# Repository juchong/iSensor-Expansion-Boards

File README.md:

# iSensor IMU Expansion Boards
## Introduction

This repository contains several expansion boards, FX3 pods, and miscellaneous circuit boards I've designed over the years to interface with ADI iSensor IMUs. All of these designs were validated at some point, but regardless, may have small issues (usually mechanical alignment)! 

### [48x, 49x Breakout Board](https://github.com/juchong/iSensor-Expansion-Boards/tree/main/48x_49x%20Breakout%20Board)

This board was designed as a smaller, more space-efficient replacement for the ADIS16IMU1/PCBZ board and provides similar functionality. All of the necessary signals are routed from the 24-pin, 1mm connector to the 16-pin, 2mm connector. 

A copy of the Rev C version of this PCB can be ordered from OshPark using this [link](https://oshpark.com/shared_projects/d1aorWWM).

### [ADXL_ADXRS Breakout Pod](https://github.com/juchong/iSensor-Expansion-Boards/tree/main/ADXL_ADXRS%20Breakout%20Pod)

This board was designed to interface with the EVAL-ADIS-FX3 (hence the "pod" nickname) and provides a generic interface for ADI accelerometers (ADXL-series devices) and gyroscopes (ADXRS-series devices) with a **digital** interface. 

A copy of the Rev A version of this PCB can be ordered from OshPark using this [link](https://oshpark.com/shared_projects/PcQ047B9).

### [FX3 Unit Test Loopback Pod](https://github.com/juchong/iSensor-Expansion-Boards/tree/main/FX3%20Unit%20Test%20Loopback%20Pod)

This board provides a compact and convenient way of verifying that the EVAL-ADIS-FX3 was manufactured correctly by looping back GPIO pins to each other. [This](https://github.com/juchong/EVAL-ADIS-FX3-Production-Test) repository contains additional software and documentation resources. 

A copy of the Rev B version of this PCB can be ordered from OshPark using this [link](https://oshpark.com/shared_projects/FAYf9S82).

### [SPI Extender](https://github.com/juchong/iSensor-Expansion-Boards/tree/main/SPI%20Extender)

These boards provided an example for using LVDS transmitters and receivers to push SPI through a CAT6 Ethernet cable (twisted pair). Using these boards, we were able to reliably communicate with an ADI IMU through 25 feet of cable. 

### [iSensor Arduino Shield](https://github.com/juchong/iSensor-Expansion-Boards/tree/main/iSensor%20Arduino%20Shield)

This shield was developed as a reference design for easily interfacing an Arduino-compatible device with most iSensor evaluation boards. The shield includes a switching regulator that can be used to power the IMU instead of relying on the host system's 3.3V supply.

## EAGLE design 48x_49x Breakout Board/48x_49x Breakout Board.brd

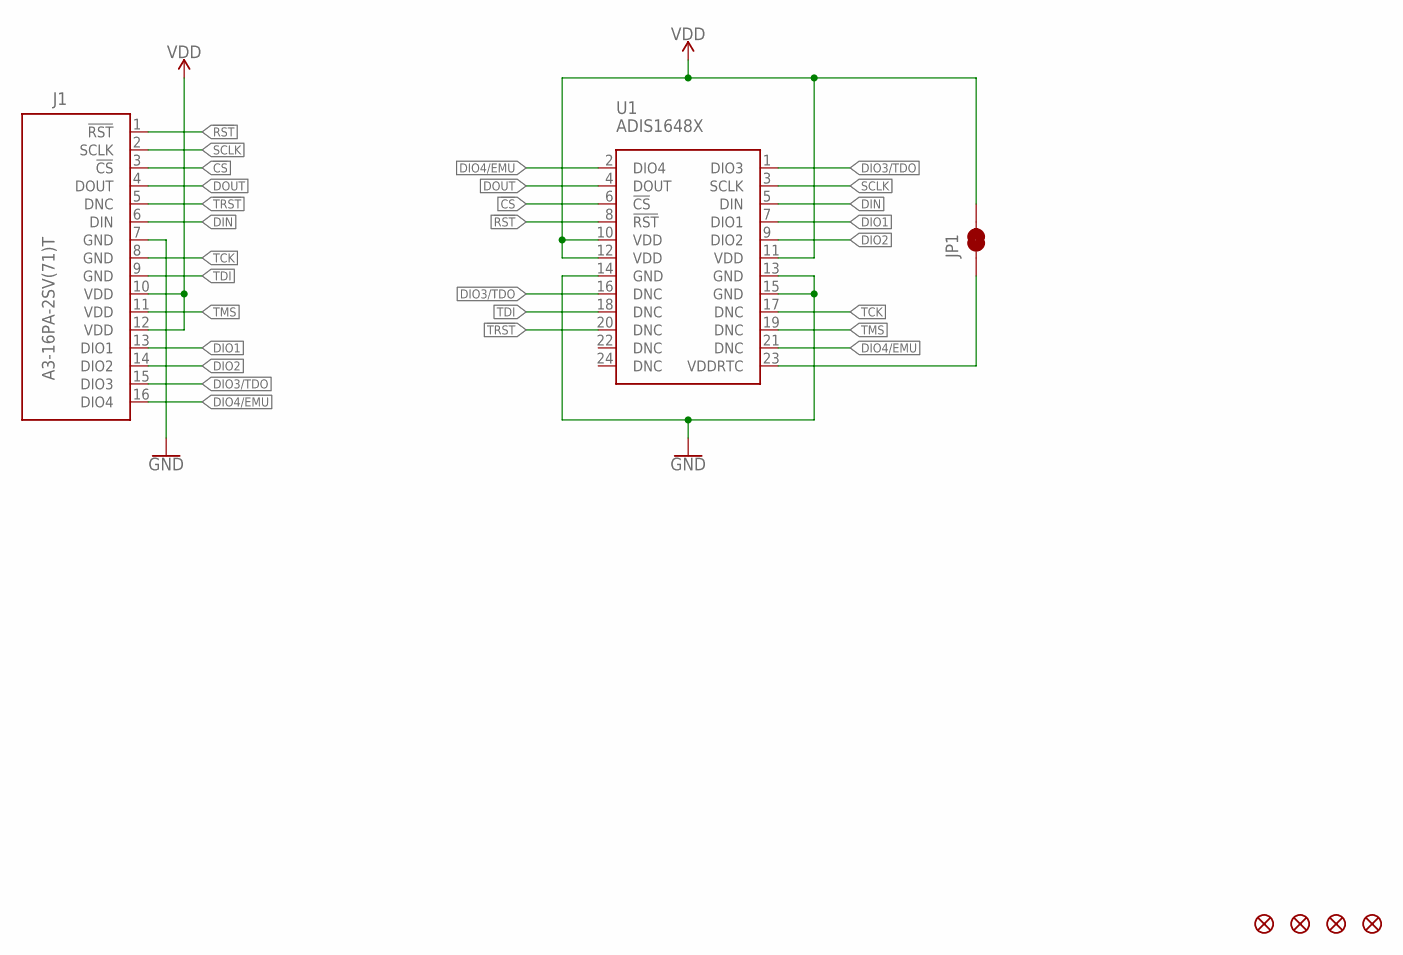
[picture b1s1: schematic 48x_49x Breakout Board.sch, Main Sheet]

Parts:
FD1, FD2, FD3, FD4: FIDUCIAL1X2; FIDUCIAL-1X2
J1: A3-16PA-2SV(71)T; A3-16PA-2SV(71)-TOP
JP1: JUMPER-SMT_2_NC_TRACE_SILK; SMT-JUMPER_2_NC_TRACE_SILK
U1: ADIS1648X

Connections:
!CS: J1.3 (!CS), U1.6 (!CS)
!RST: J1.1 (!RST), U1.8 (!RST)
!TRST: J1.5 (DNC), U1.20 (DNC)
DIN: J1.6 (DIN), U1.5 (DIN)
DIO1: J1.13 (DIO1), U1.7 (DIO1)
DIO2: J1.14 (DIO2), U1.9 (DIO2)
DIO3/TDO: J1.15 (DIO3), U1.1 (DIO3), U1.16 (DNC)
DIO4/EMU: J1.16 (DIO4), U1.2 (DIO4), U1.21 (DNC)
DOUT: J1.4 (DOUT), U1.4 (DOUT)
GND: J1.7 (GND), U1.13 (GND), U1.14 (GND), U1.15 (GND)
unnamed: JP1.1, U1.23 (VDDRTC)
SCLK: J1.2 (SCLK), U1.3 (SCLK)
TCK: J1.8 (GND), U1.17 (DNC)
TDI: J1.9 (GND), U1.18 (DNC)
TMS: J1.11 (VDD), U1.19 (DNC)
VDD: J1.10 (VDD), J1.12 (VDD), JP1.2, U1.10 (VDD), U1.11 (VDD), U1.12 (VDD)

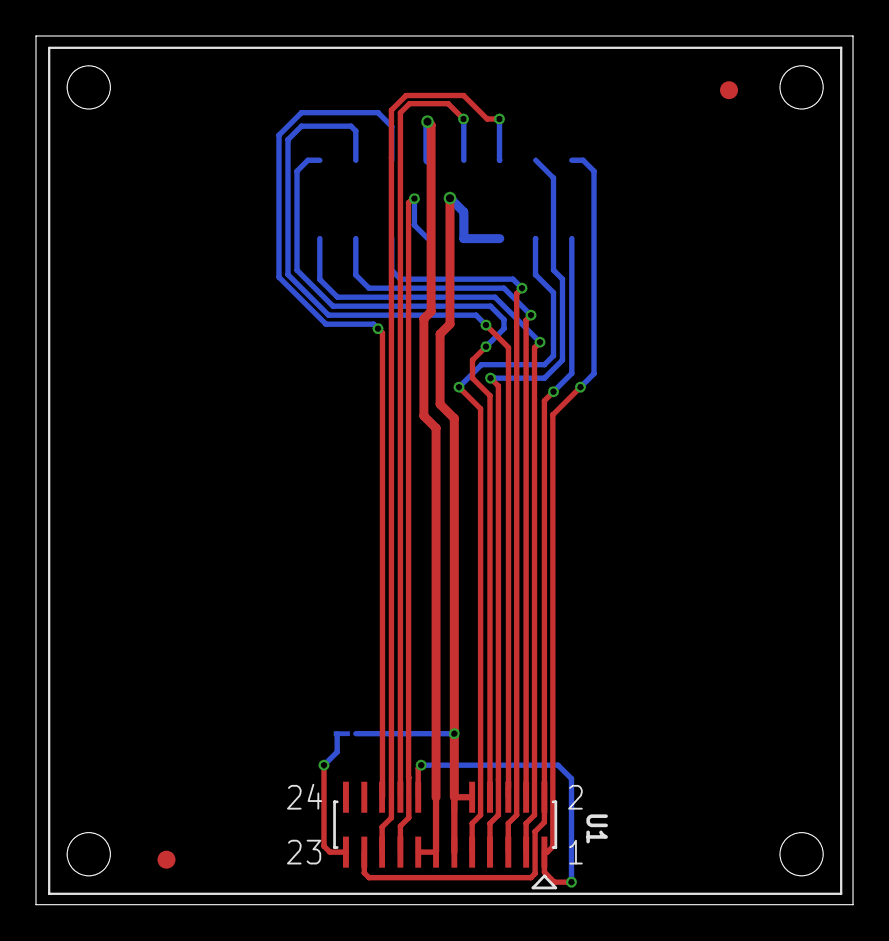
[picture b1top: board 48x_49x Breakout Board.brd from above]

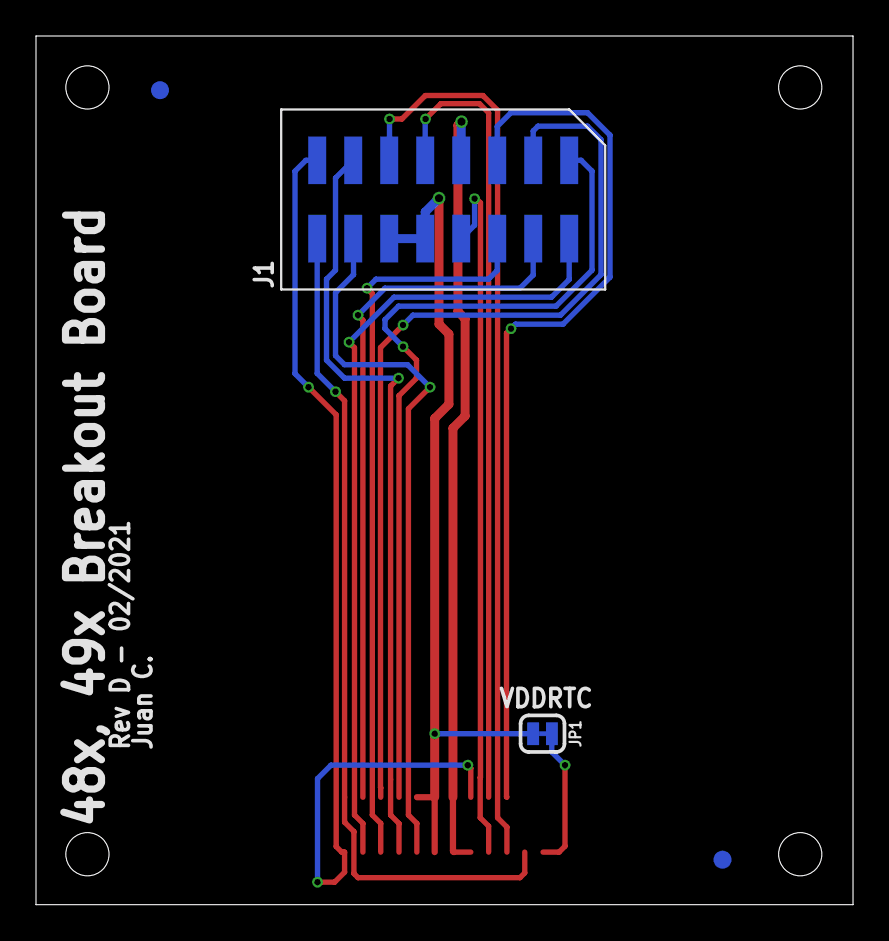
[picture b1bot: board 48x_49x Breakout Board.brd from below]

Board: 2 copper layers, 45.4 x 48.3 mm, 7 parts (4 on the bottom side), 16 nets.

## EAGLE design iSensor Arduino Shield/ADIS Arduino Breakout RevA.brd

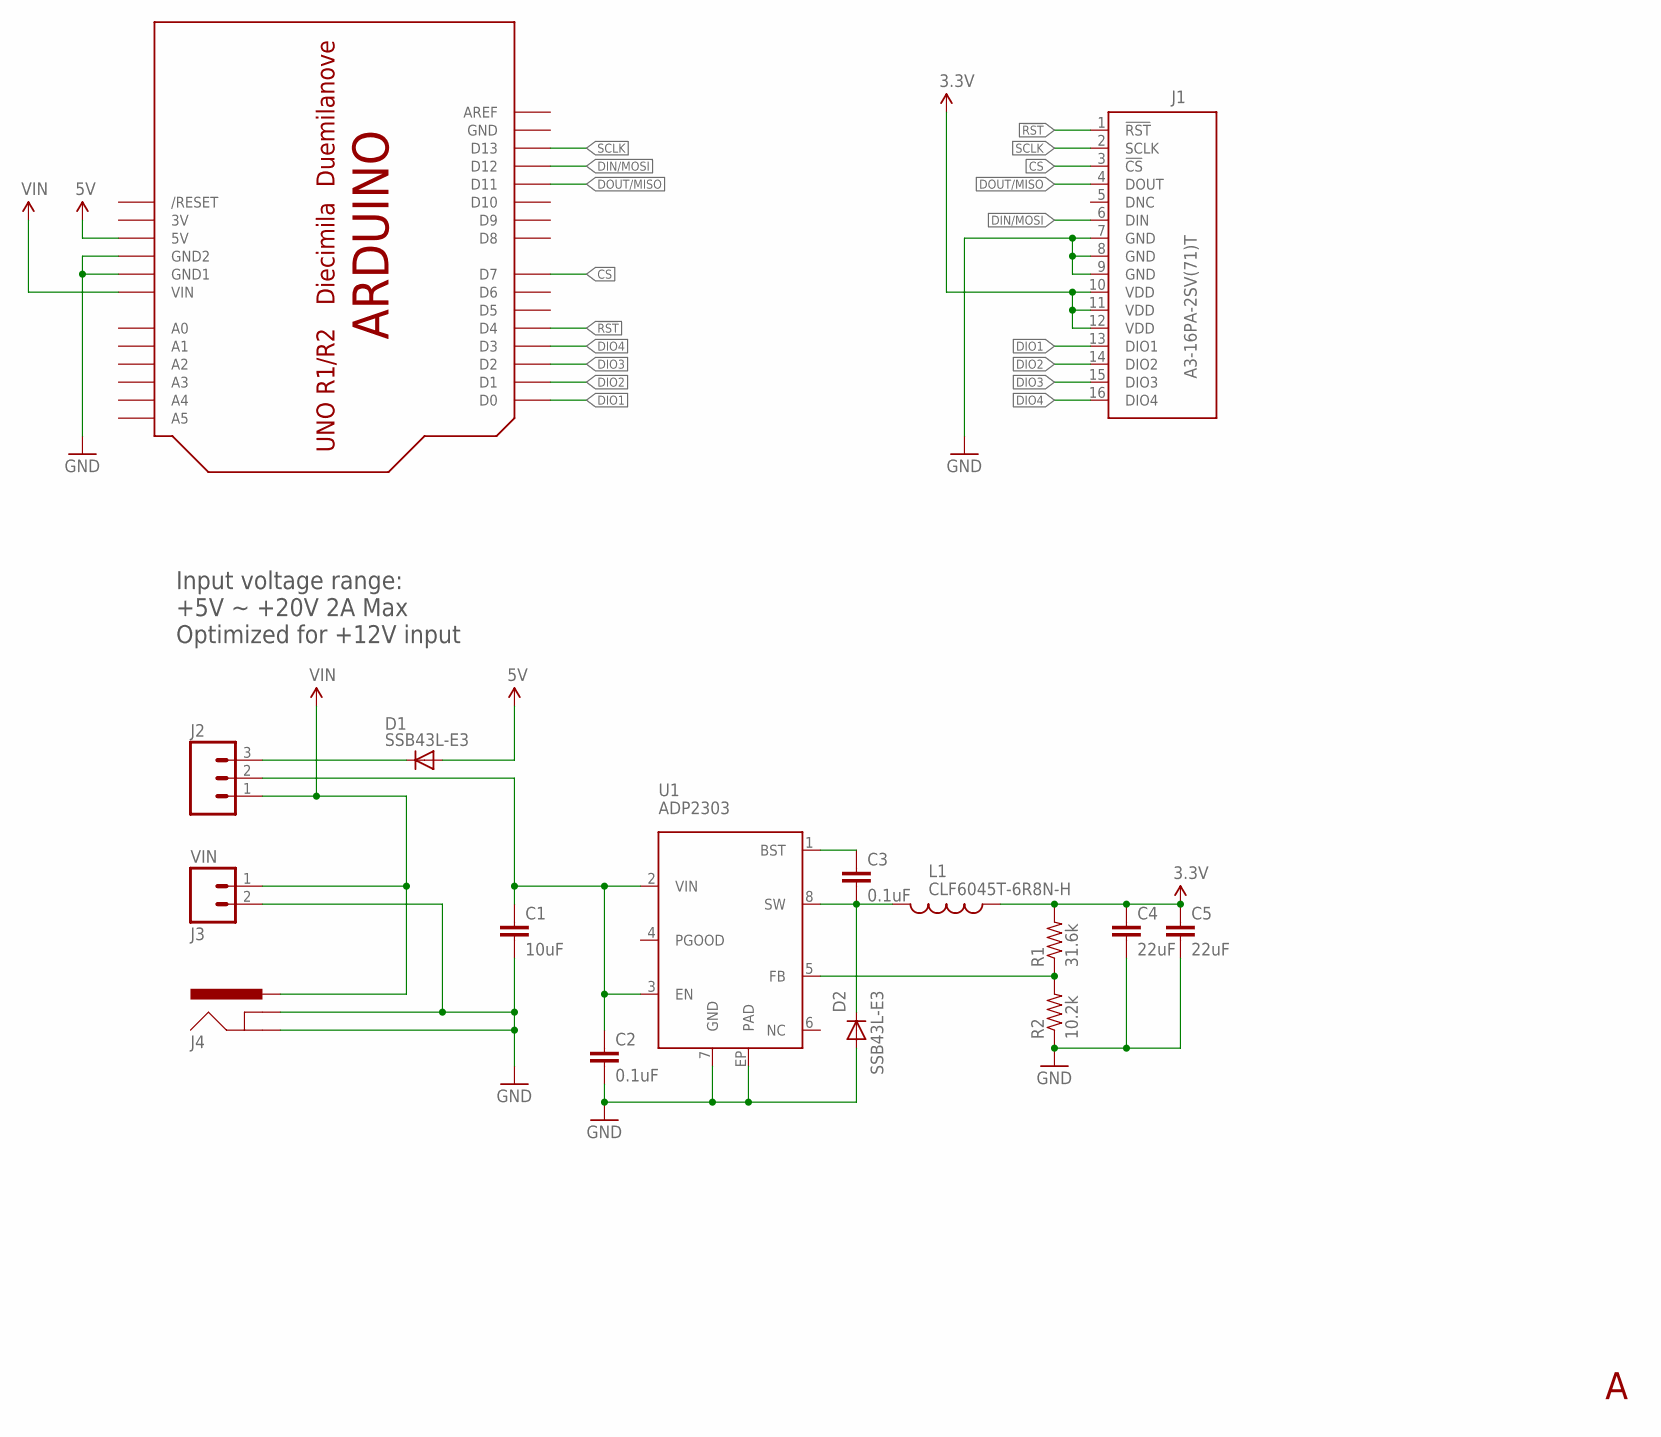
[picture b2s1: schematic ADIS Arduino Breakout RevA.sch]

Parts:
C1: 10uF; 1206; PARTNO F931C106MAA
C2, C3: 0.1uF; 0603-CAP; PARTNO CL10B104KB8NNNC
C4, C5: 22uF; 1210; PARTNO GRM32ER61C226KE20L
D1, D2: SSB43L-E3; DO214AA; PARTNO SSB43L-E3/52T
J1: A3-16PA-2SV(71)T; A3-16PA-2SV(71)-TOP; PARTNO A3-16PA-2SV(71)
J2: M03PTH; 1X03; PARTNO PREC003SAAN-RC
J3: VIN; SCREWTERMINAL-3.5MM-2; PARTNO 20020327-C021B01LF
J4: POWER_JACKPTH_LOCK; POWER_JACK_PTH_LOCK; PARTNO PJ-002AH
J5: ARDUINOUNO; ARDUINO
L1: CLF6045T-6R8N-H; CLF6045-H; PARTNO CLF6045T-6R8N-H
R1: 31.6k; 0603-RES; PARTNO ERJ-3EKF3162V
R2: 10.2k; 0603-RES; PARTNO ERJ-3EKF1022V
U1: ADP2303; SOIC-8-PAD; PARTNO ADP2303ARDZ

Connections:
3.3V: C4.1, C5.1, J1.10 (VDD), J1.11 (VDD), J1.12 (VDD), L1.P$1 (1), R1.2
3V: J5.3V
5V: D1.A, J5.5V
!RST: J1.1 (!RST), J5.D4
CS: J1.3 (!CS), J5.D7
DIN/MOSI: J1.6 (DIN), J5.D12
DIO1: J1.13 (DIO1), J5.D0
DIO2: J1.14 (DIO2), J5.D1
DIO3: J1.15 (DIO3), J5.D2
DIO4: J1.16 (DIO4), J5.D3
DOUT/MISO: J1.4 (DOUT), J5.D11
GND: C1.2, C2.2, C4.2, C5.2, D2.A, J1.7 (GND), J1.8 (GND), J1.9 (GND), J3.2, J4.GND, J4.GNDBREAK, J5.GND, J5.GND1, J5.GND2, R2.1, U1.7 (GND), U1.EP (PAD)
unnamed: R1.1, R2.2, U1.5 (FB)
unnamed: C3.2, D2.C, L1.P$2 (2), U1.8 (SW)
unnamed: C3.1, U1.1 (BST)
unnamed: C1.1, C2.1, J2.2, U1.2 (VIN), U1.3 (EN)
unnamed: D1.C, J2.3
SCLK: J1.2 (SCLK), J5.D13
VIN: J2.1, J3.1, J4.PWR, J5.VIN

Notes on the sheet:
Input voltage range: +5V ~ +20V 2A Max Optimized for +12V input

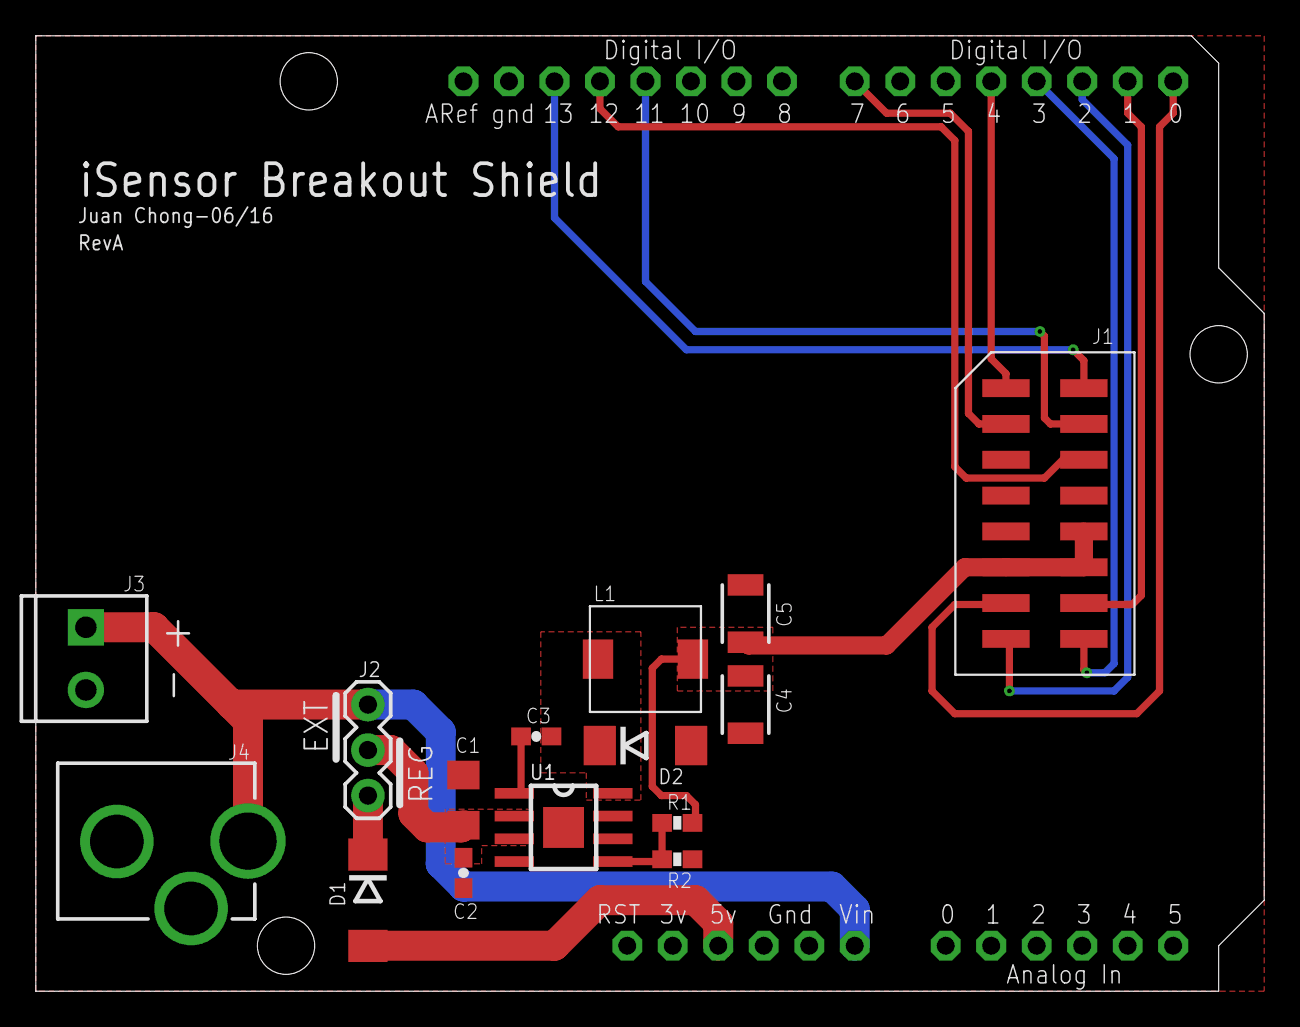
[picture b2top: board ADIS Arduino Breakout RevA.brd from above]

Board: 2 copper layers, 68.6 x 53.3 mm, 16 parts (0 on the bottom side), 18 nets.

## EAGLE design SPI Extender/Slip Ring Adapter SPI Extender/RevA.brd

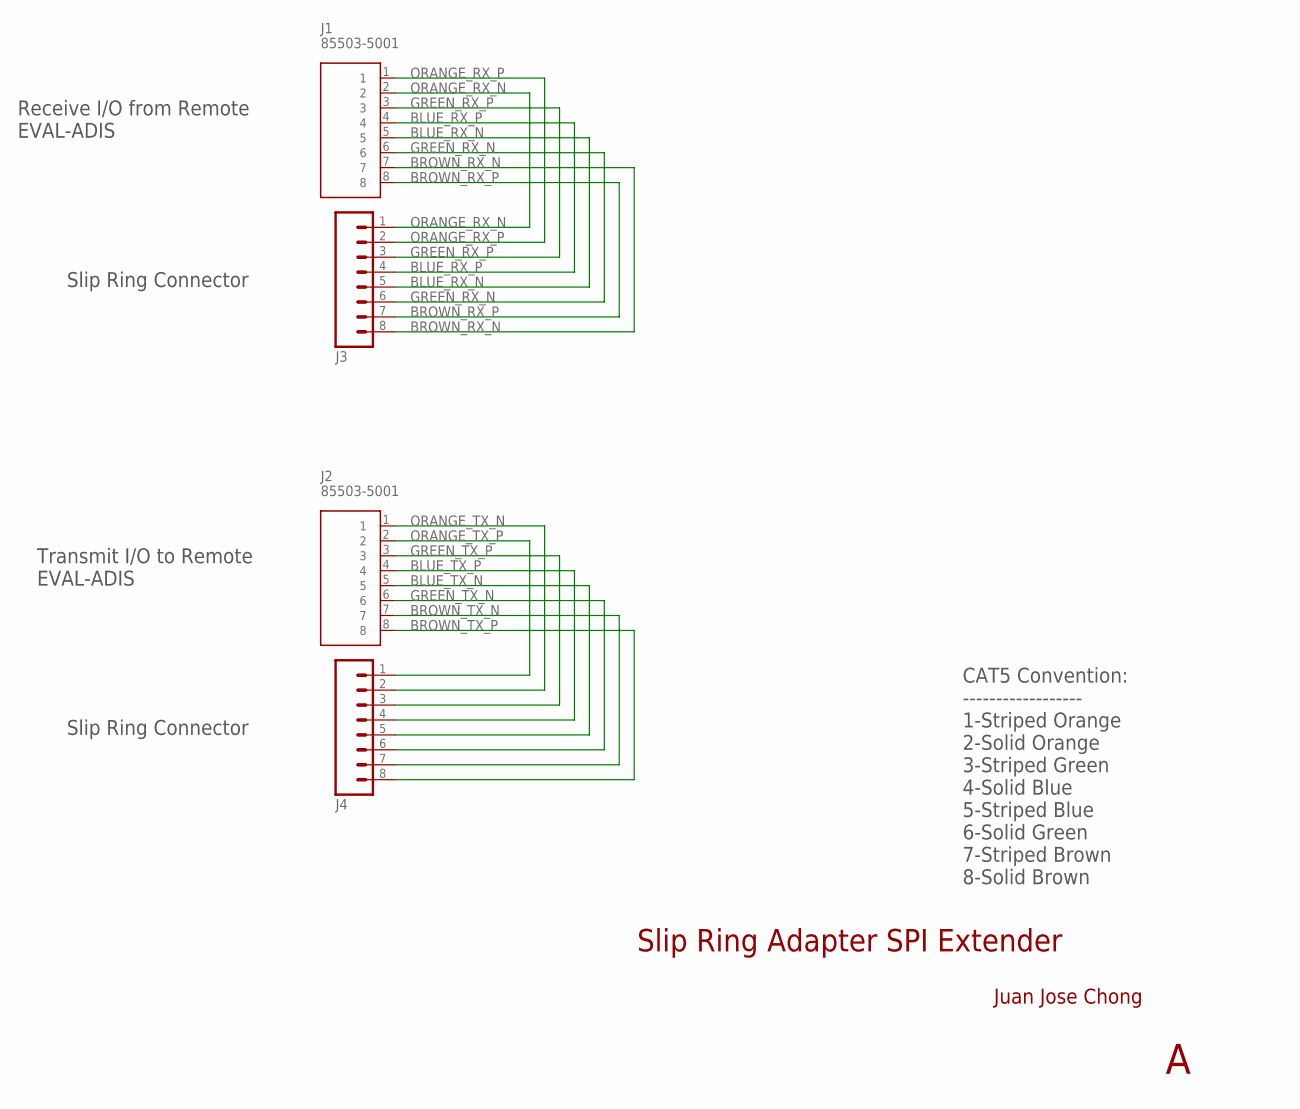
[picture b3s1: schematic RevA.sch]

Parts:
J1, J2: 85503-5001; PARTNO 855035001
J3, J4: M08LOCK; 1X08_LOCK

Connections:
BLUE_RX_N: J1.5, J3.5
BLUE_RX_P: J1.4, J3.4
BLUE_TX_N: J2.5, J4.5
BLUE_TX_P: J2.4, J4.4
BROWN_RX_N: J1.7, J3.8
BROWN_RX_P: J1.8, J3.7
BROWN_TX_N: J2.7, J4.7
BROWN_TX_P: J2.8, J4.8
GREEN_RX_N: J1.6, J3.6
GREEN_RX_P: J1.3, J3.3
GREEN_TX_N: J2.6, J4.6
GREEN_TX_P: J2.3, J4.3
ORANGE_RX_N: J1.2, J3.1
ORANGE_RX_P: J1.1, J3.2
ORANGE_TX_N: J2.1, J4.2
ORANGE_TX_P: J2.2, J4.1

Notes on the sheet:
Receive I/O from Remote EVAL-ADIS
Transmit I/O to Remote EVAL-ADIS
Slip Ring Connector
Slip Ring Adapter SPI Extender
Juan Jose Chong
CAT5 Convention: ------------------ 1-Striped Orange 2-Solid Orange 3-Striped Green 4-Solid Blue 5-Striped Blue 6-Solid Green 7-Striped Brown 8-Solid Brown

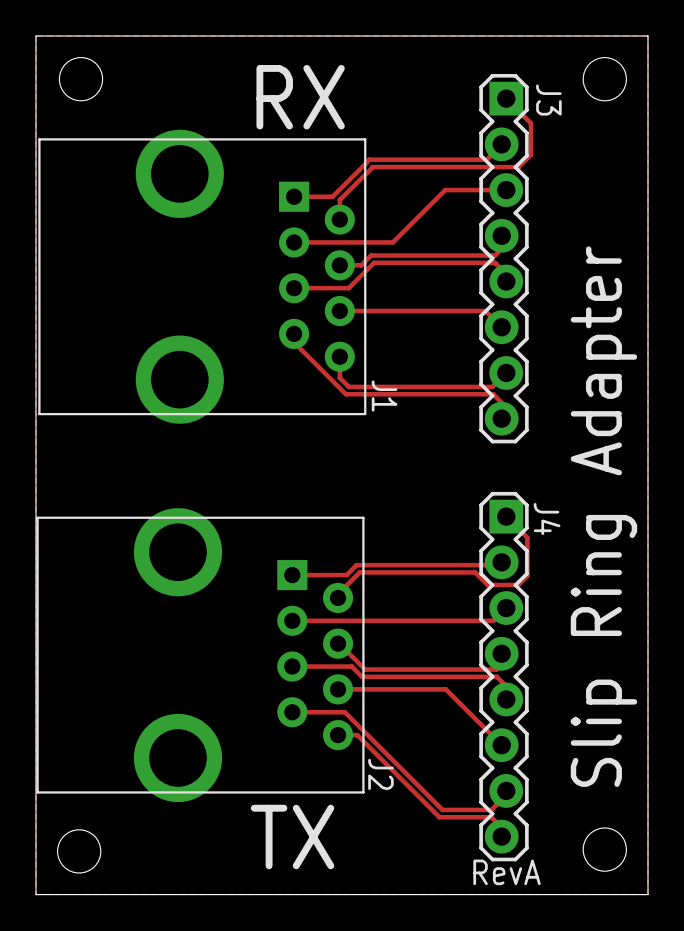
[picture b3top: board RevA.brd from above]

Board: 2 copper layers, 34.0 x 47.7 mm, 4 parts (0 on the bottom side), 16 nets.

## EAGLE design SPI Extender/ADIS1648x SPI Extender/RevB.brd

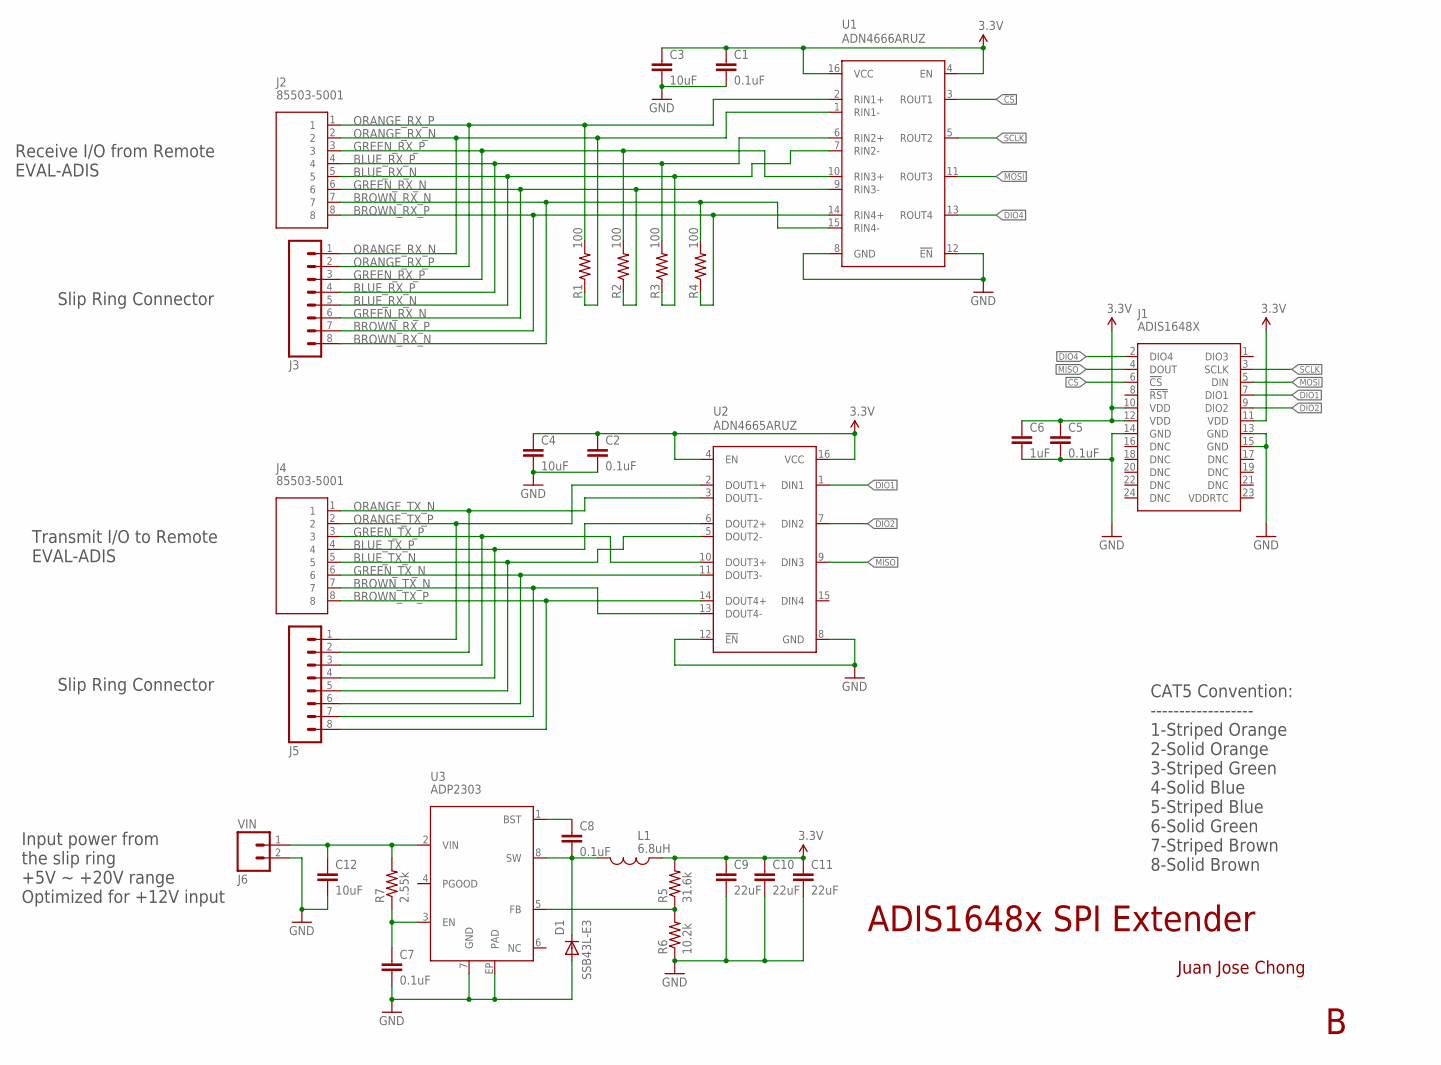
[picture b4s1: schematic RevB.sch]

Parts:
C1, C2, C5, C7, C8: 0.1uF; 0603-CAP; PARTNO CL10B104KB8NNNC
C3, C4: 10uF; 1206; PARTNO F931C106MAA
C6: 1uF; 0603-CAP; PARTNO GRM188R61C105KA93D
C9, C10, C11: 22uF; 1210; PARTNO TLJA476M010R0600
C12: 10uF; 1206; PARTNO TLJA476M010R0600
D1: SSB43L-E3; DO214AA; PARTNO SSB43L-E3/52T
J1: ADIS1648X; PARTNO CLM-112-02-L-D
J2, J4: 85503-5001; PARTNO 855035001
J3, J5: M08LOCK; 1X08_LOCK; PARTNO PREC008SAAN-RC
J6: VIN; SCREWTERMINAL-3.5MM-2; PARTNO 20020327-C021B01LF
L1: 6.8uH; VLF10040; PARTNO VLF10040T-6R8N4R5
R1, R2, R3, R4: 100; 0603-RES; PARTNO ERJ-3EKF1000V
R5: 31.6k; 0603-RES; PARTNO ERJ-3EKF3162V
R6: 10.2k; 0603-RES; PARTNO ERJ-3EKF1022V
R7: 2.55k; 0603-RES; PARTNO ERJ-3EKF2551V
U1: ADN4666ARUZ; TSSOP-16; PARTNO ADN4666ARUZ
U2: ADN4665ARUZ; TSSOP-16; PARTNO ADN4665ARUZ
U3: ADP2303; SOIC-8-PAD; PARTNO ADP2303ARDZ

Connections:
3.3V: C1.1, C2.1, C3.1, C4.1, C5.1, C6.1, C9.1, C10.1, C11.1, J1.10 (VDD), J1.11 (VDD), J1.12 (VDD), L1.P$1 (1), R5.2, U1.4 (EN), U1.16 (VCC), U2.4 (EN), U2.16 (VCC)
!CS: J1.6 (!CS), U1.3 (ROUT1)
BLUE_RX_N: J2.5, J3.5, R3.1, U1.7 (RIN2-)
BLUE_RX_P: J2.4, J3.4, R3.2, U1.6 (RIN2+)
BLUE_TX_N: J4.5, J5.5, U2.5 (DOUT2-)
BLUE_TX_P: J4.4, J5.4, U2.6 (DOUT2+)
BROWN_RX_N: J2.7, J3.8, R4.2, U1.15 (RIN4-)
BROWN_RX_P: J2.8, J3.7, R4.1, U1.14 (RIN4+)
BROWN_TX_N: J4.7, J5.7, U2.13 (DOUT4-)
BROWN_TX_P: J4.8, J5.8, U2.14 (DOUT4+)
DIO1: J1.7 (DIO1), U2.1 (DIN1)
DIO2: J1.9 (DIO2), U2.7 (DIN2)
DIO4: J1.2 (DIO4), U1.13 (ROUT4)
GND: C1.2, C2.2, C3.2, C4.2, C5.2, C6.2, C7.2, C9.2, C10.2, C11.2, C12.2, D1.A, J1.13 (GND), J1.14 (GND), J1.15 (GND), J6.2, R6.1, U1.8 (GND), U1.12 (!EN), U2.8 (GND), U2.12 (!EN), U3.7 (GND), U3.EP (PAD)
GREEN_RX_N: J2.6, J3.6, R2.1, U1.9 (RIN3-)
GREEN_RX_P: J2.3, J3.3, R2.2, U1.10 (RIN3+)
GREEN_TX_N: J4.6, J5.6, U2.11 (DOUT3-)
GREEN_TX_P: J4.3, J5.3, U2.10 (DOUT3+)
MISO: J1.4 (DOUT), U2.9 (DIN3)
MOSI: J1.5 (DIN), U1.11 (ROUT3)
unnamed: C12.1, J6.1, R7.2, U3.2 (VIN)
unnamed: R5.1, R6.2, U3.5 (FB)
unnamed: C8.2, D1.C, L1.P$2 (2), U3.8 (SW)
unnamed: C8.1, U3.1 (BST)
unnamed: C7.1, R7.1, U3.3 (EN)
ORANGE_RX_N: J2.2, J3.1, R1.1, U1.1 (RIN1-)
ORANGE_RX_P: J2.1, J3.2, R1.2, U1.2 (RIN1+)
ORANGE_TX_N: J4.1, J5.2, U2.3 (DOUT1-)
ORANGE_TX_P: J4.2, J5.1, U2.2 (DOUT1+)
SCLK: J1.3 (SCLK), U1.5 (ROUT2)

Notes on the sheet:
Receive I/O from Remote EVAL-ADIS
Transmit I/O to Remote EVAL-ADIS
Slip Ring Connector
Input power from the slip ring +5V ~ +20V range Optimized for +12V input
ADIS1648x SPI Extender
Juan Jose Chong
CAT5 Convention: ------------------ 1-Striped Orange 2-Solid Orange 3-Striped Green 4-Solid Blue 5-Striped Blue 6-Solid Green 7-Striped Brown 8-Solid Brown

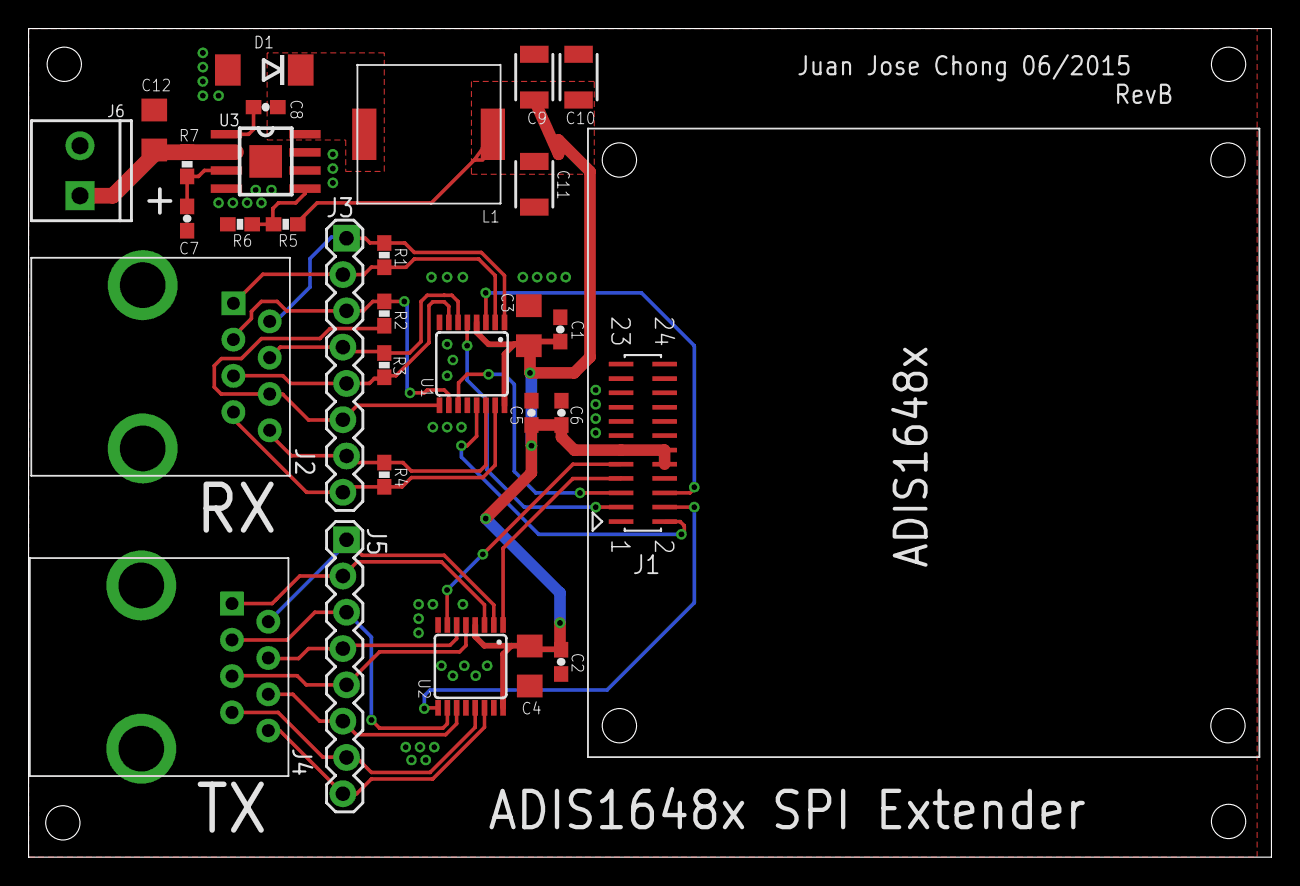
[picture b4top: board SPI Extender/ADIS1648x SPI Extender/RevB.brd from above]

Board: 2 copper layers, 87.0 x 58.0 mm, 30 parts (0 on the bottom side), 30 nets.

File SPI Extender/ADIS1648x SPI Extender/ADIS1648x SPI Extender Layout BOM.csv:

Qty-1,Part References,Value,Package,Mfg Part Num,Mfg Name,VID,Vendor Part Num,Description,Pkg Code,,XREF
2,"J3, J5",,1X08_LOCK,PREC008SAAN-RC,Sullins Connector Solutions,DK,S1012EC-08-ND,CONN HEADER .100"" SNGL STR 8POS,1X08,*,REF193
5,"C1, C2, C5, C7, C8",0.1uF,0603-CAP,CL10B104KB8NNNC,Samsung Electro-Mechanics America,DK,1276-1000-1-ND,CAP CER 0.1UF 50V 10% X7R 0603,0603-CAP,*,REF134
1,"C6",1uF,0603-CAP,GRM188R61C105KA93D,Murata Electronics North America,DK,490-1536-1-ND,CAP CER 1UF 16V 10% X5R 0603,C0603,*,REF82
1,"R7",2.55k,0603-RES,ERJ-3EKF2551V,Panasonic Electronic Components,DK,P2.55KHCT-ND,RES SMD 2.55K OHM 1% 1/10W 0603,0603-RES,*,REF190
1,"L1",6.8uH,VLF10040,VLF10040T-6R8N4R5,TDK Corporation,DK,445-3561-1-ND,FIXED IND 6.8UH 4.5A 23.8 MOHM,0.394"" L x 0.382"" W (10.00mm x 9.70mm),*,REF183
1,"R6",10.2k,0603-RES,ERJ-3EKF1022V,Panasonic Electronic Components,DK,P10.2KHCT-ND,RES SMD 10.2K OHM 1% 1/10W 0603,0603-RES,*,REF189
2,"C3, C4",10uF,1206,F931C106MAA,AVX Corporation,DK,478-8237-1-ND,CAP TANT 10UF 16V 20% 1206,1206-RES,*,REF179
1,"C12",10uF,1206,TLJA476M010R0600,AVX Corporation,DK,478-9009-1-ND,CAP TANT 47UF 10V 20% 1206,1206-RES,*,REF180
3,"C9, C10, C11",22uF,1210,TLJA476M010R0600,AVX Corporation,DK,478-9009-1-ND,CAP TANT 47UF 10V 20% 1206,1206-RES,*,REF180
1,"R5",31.6k,0603-RES,ERJ-3EKF3162V,Panasonic Electronic Components,DK,P31.6KHCT-ND,RES SMD 31.6K OHM 1% 1/10W 0603,0603-RES,*,REF188
4,"R1, R2, R3, R4",100,0603-RES,ERJ-3EKF1000V,Panasonic Electronic Components,DK,P100HCT-ND,RES SMD 100 OHM 1% 1/10W 0603,0603-RES,*,REF187
2,"J2, J4",85503-5001,85503-5001,855035001,Molex Inc.,DK,WM4016-ND,CONN MOD JACK 8P8C R/A UNSHLD,RJ45-8P8C,*,REF182
1,"J1",ADIS1648X,ADIS1648X,CLM-112-02-L-D,Samtec Inc,DK,SAM1129-12-ND,CONN RCPT LOPRO DL 24POS 1MM SMD,CLM24,*,REF192
1,"U2",ADN4665ARUZ,TSSOP-16,ADN4665ARUZ,Analog Devices Inc,DK,ADN4665ARUZ-ND,IC DRIVER DIFF LVDS QUAD 16TSSOP,TSSOP16,*,REF185
1,"U1",ADN4666ARUZ,TSSOP-16,ADN4666ARUZ,Analog Devices Inc,DK,ADN4666ARUZ-ND,IC RCVR DIFF LVDS QUAD 16TSSOP,TSSOP16,*,REF184
1,"U3",ADP2303,SOIC-8-PAD,ADP2303ARDZ,Analog Devices Inc,DK,ADP2303ARDZ-ND,IC REG BUCK ADJ 3A 8SOIC,8-SOIC-EP,*,REF186
1,"D1",SSB43L-E3,DO214AA,SSB43L-E3/52T,Vishay Semiconductor Diodes Division,DK,SSB43L-E3/52TGICT-ND,DIODE SCHOTTKY 30V 4A DO214AA,DO-214AA,*,REF181
1,"J6",VIN,SCREWTERMINAL-3.5MM-2,20020327-C021B01LF,FCI,DK,609-4725-ND,3.5MM TERMINAL BLOCK -55~110C,3.5MM,*,REF191

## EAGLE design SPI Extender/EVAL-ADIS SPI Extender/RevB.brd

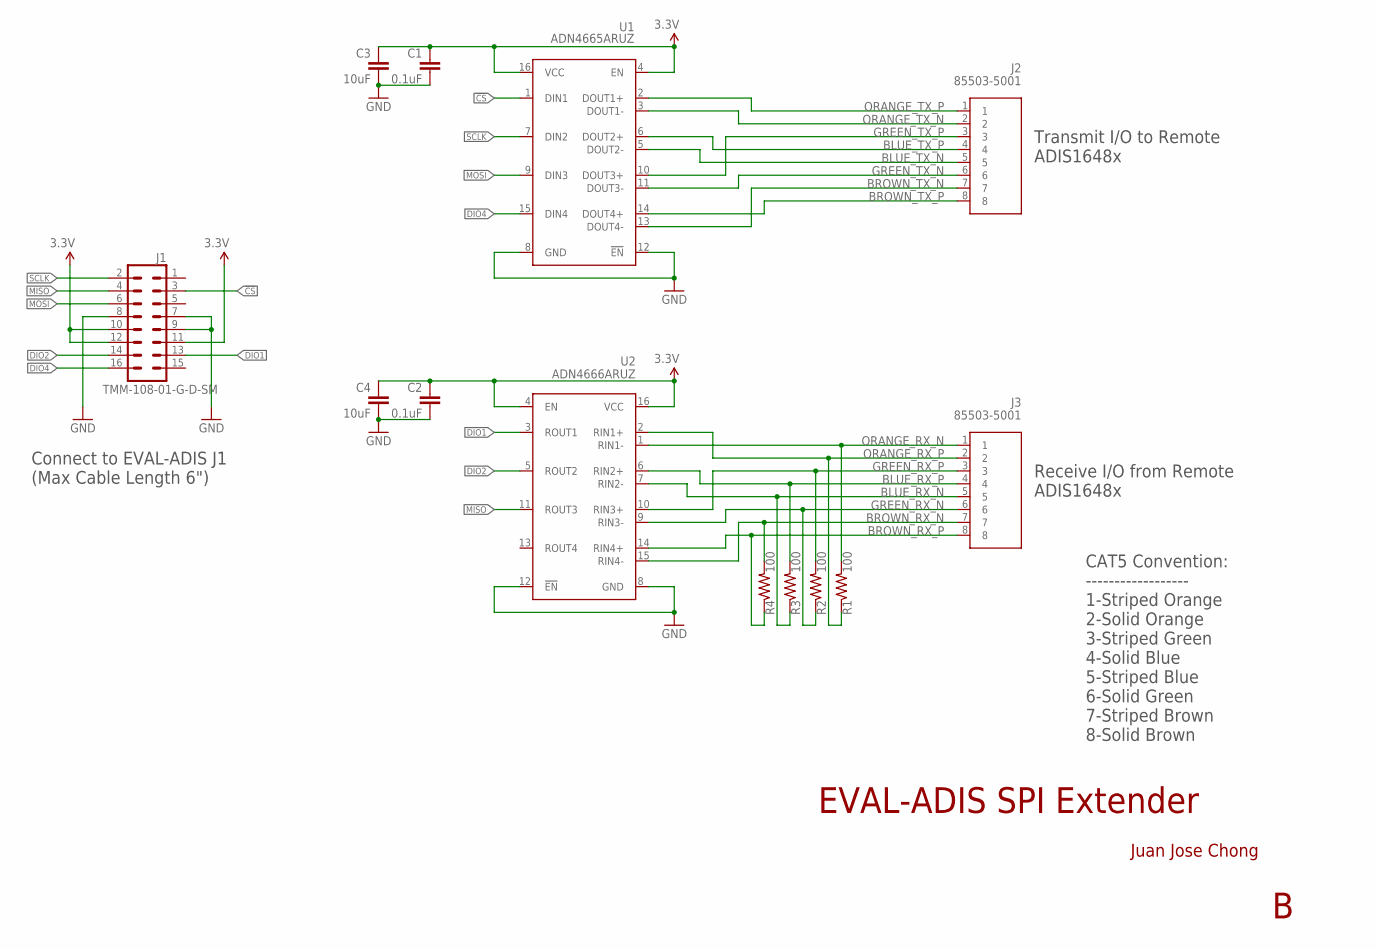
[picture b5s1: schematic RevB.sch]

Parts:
C1, C2: 0.1uF; 0805; PARTNO CL10B104KB8NNNC
C3, C4: 10uF; 1206; PARTNO F931C106MAA
J1: TMM-108-01-G-D-SM; TMM-108-XX-X-D; PARTNO TMM-108-01-G-D-SM
J2, J3: 85503-5001; PARTNO 855035001
R1, R2, R3, R4: 100; 0603-RES; PARTNO ERJ-3EKF1000V
U1: ADN4665ARUZ; TSSOP-16; PARTNO ADN4665ARUZ
U2: ADN4666ARUZ; TSSOP-16; PARTNO ADN4666ARUZ

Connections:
3.3V: C1.1, C2.1, C3.1, C4.1, J1.10, J1.11, J1.12, U1.4 (EN), U1.16 (VCC), U2.4 (EN), U2.16 (VCC)
!CS: J1.3, U1.1 (DIN1)
BLUE_RX_N: J3.5, R3.1, U2.7 (RIN2-)
BLUE_RX_P: J3.4, R3.2, U2.6 (RIN2+)
BLUE_TX_N: J2.5, U1.5 (DOUT2-)
BLUE_TX_P: J2.4, U1.6 (DOUT2+)
BROWN_RX_N: J3.7, R4.2, U2.15 (RIN4-)
BROWN_RX_P: J3.8, R4.1, U2.14 (RIN4+)
BROWN_TX_N: J2.7, U1.13 (DOUT4-)
BROWN_TX_P: J2.8, U1.14 (DOUT4+)
DIO1: J1.13, U2.3 (ROUT1)
DIO2: J1.14, U2.5 (ROUT2)
DIO4: J1.16, U1.15 (DIN4)
GND: C1.2, C2.2, C3.2, C4.2, J1.7, J1.8, J1.9, U1.8 (GND), U1.12 (!EN), U2.8 (GND), U2.12 (!EN)
GREEN_RX_N: J3.6, R2.1, U2.9 (RIN3-)
GREEN_RX_P: J3.3, R2.2, U2.10 (RIN3+)
GREEN_TX_N: J2.6, U1.11 (DOUT3-)
GREEN_TX_P: J2.3, U1.10 (DOUT3+)
MISO: J1.4, U2.11 (ROUT3)
MOSI: J1.6, U1.9 (DIN3)
ORANGE_RX_N: J3.1, R1.2, U2.1 (RIN1-)
ORANGE_RX_P: J3.2, R1.1, U2.2 (RIN1+)
ORANGE_TX_N: J2.2, U1.3 (DOUT1-)
ORANGE_TX_P: J2.1, U1.2 (DOUT1+)
SCLK: J1.2, U1.7 (DIN2)

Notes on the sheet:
EVAL-ADIS SPI Extender
Juan Jose Chong
CAT5 Convention: ------------------ 1-Striped Orange 2-Solid Orange 3-Striped Green 4-Solid Blue 5-Striped Blue 6-Solid Green 7-Striped Brown 8-Solid Brown
Connect to EVAL-ADIS J1 (Max Cable Length 6")
Transmit I/O to Remote ADIS1648x
Receive I/O from Remote ADIS1648x

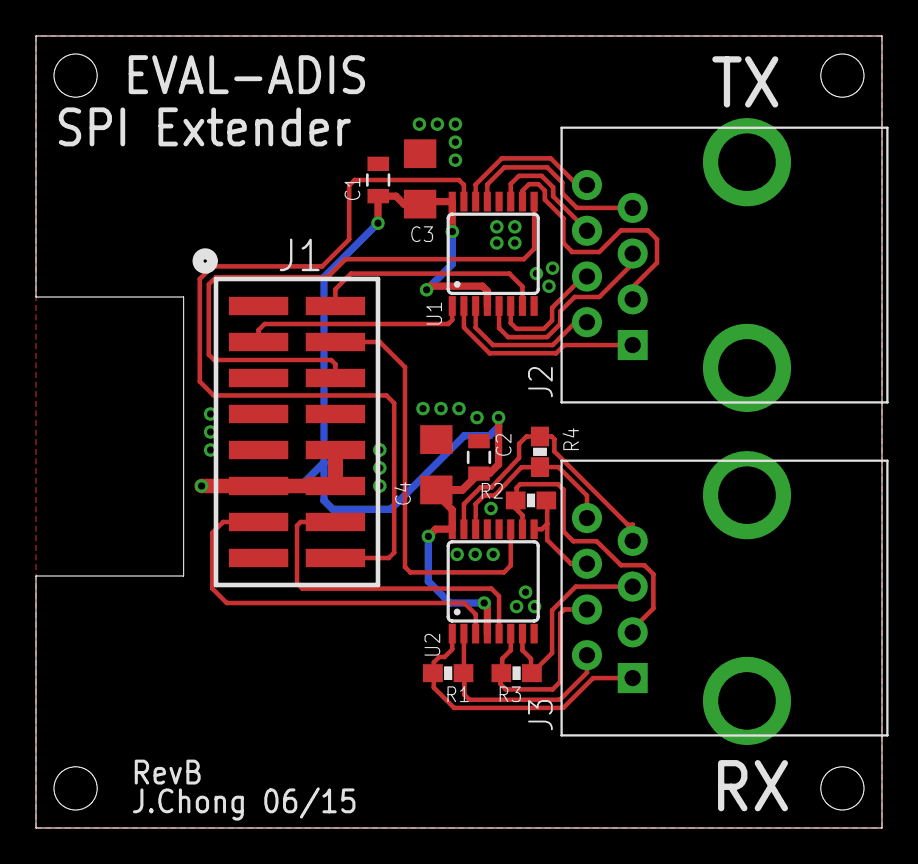
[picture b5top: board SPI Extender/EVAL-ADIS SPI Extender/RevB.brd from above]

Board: 2 copper layers, 47.0 x 44.0 mm, 13 parts (0 on the bottom side), 25 nets.

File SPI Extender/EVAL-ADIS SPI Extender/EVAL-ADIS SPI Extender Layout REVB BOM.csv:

Qty-1,Part References,Value,Package,Mfg Part Num,Mfg Name,VID,Vendor Part Num,Description,Pkg Code,,XREF
2,"C1, C2",0.1uF,0805,CL10B104KB8NNNC,Samsung Electro-Mechanics America,DK,1276-1000-1-ND,CAP CER 0.1UF 50V 10% X7R 0603,0603-CAP,*,REF134
2,"C3, C4",10uF,1206,F931C106MAA,AVX Corporation,DK,478-8237-1-ND,CAP TANT 10UF 16V 20% 1206,1206-RES,*,REF179
4,"R1, R2, R3, R4",100,0603-RES,ERJ-3EKF1000V,Panasonic Electronic Components,DK,P100HCT-ND,RES SMD 100 OHM 1% 1/10W 0603,0603-RES,*,REF187
2,"J2, J3",85503-5001,85503-5001,855035001,Molex Inc.,DK,WM4016-ND,CONN MOD JACK 8P8C R/A UNSHLD,RJ45-8P8C,*,REF182
1,"U1",ADN4665ARUZ,TSSOP-16,ADN4665ARUZ,Analog Devices Inc,DK,ADN4665ARUZ-ND,IC DRIVER DIFF LVDS QUAD 16TSSOP,TSSOP16,*,REF185
1,"U2",ADN4666ARUZ,TSSOP-16,ADN4666ARUZ,Analog Devices Inc,DK,ADN4666ARUZ-ND,IC RCVR DIFF LVDS QUAD 16TSSOP,TSSOP16,*,REF184
1,"J1",TMM-108-01-G-D-SM,TMM-108-XX-X-D,TMM-108-01-G-D-SM,Samtec Inc,DK,SAM1167-08-ND,CONN HEADER 16POS DUAL 2MM SMD,2X08 2MM SMD,*,REF194

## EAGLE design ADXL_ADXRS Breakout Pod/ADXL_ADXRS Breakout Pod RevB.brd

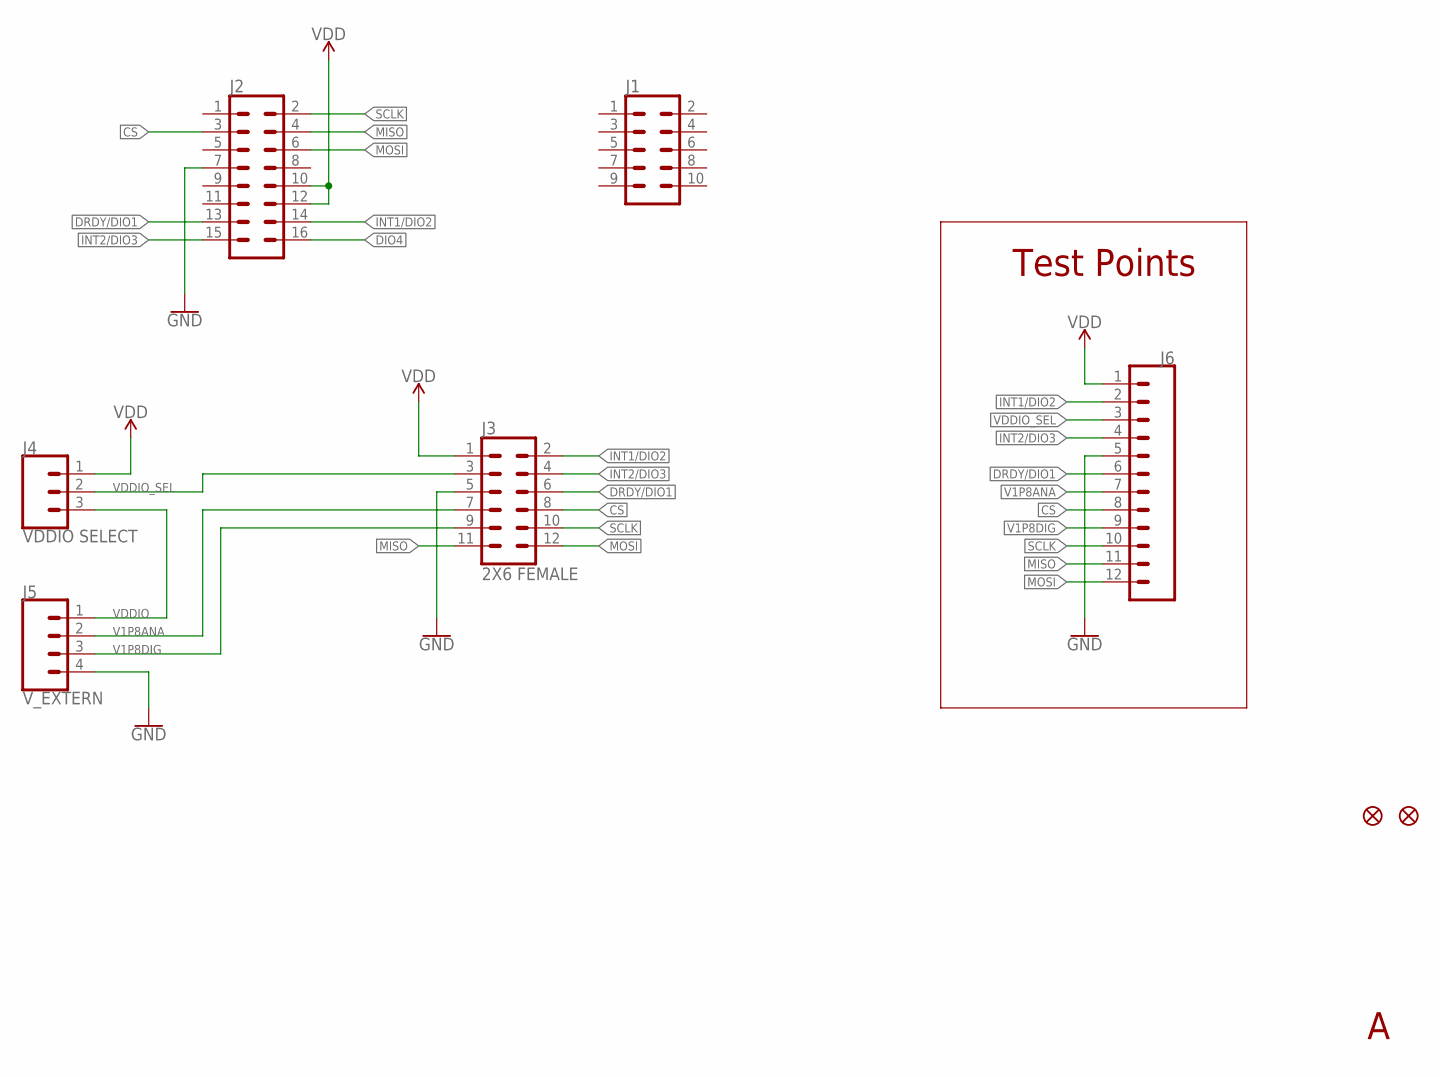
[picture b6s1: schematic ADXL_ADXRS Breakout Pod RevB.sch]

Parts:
FD1, FD2: FIDUCIAL1X2; FIDUCIAL-1X2
J1: CONN_05X2_2MM_FEMALE; M22-6550542R
J2: CONN_08X2_2MM_FEMALE; M22-6550842R
J3: 2X6 FEMALE; 2X6
J4: VDDIO SELECT; 1X03
J5: V_EXTERN; 1X04
J6: CONN_12; 1X12

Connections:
CS: J2.3, J3.8, J6.8
DIO4: J2.16
DRDY/DIO1: J2.13, J3.6, J6.6
GND: J2.7, J3.5, J5.4, J6.5
INT1/DIO2: J2.14, J3.2, J6.2
INT2/DIO3: J2.15, J3.4, J6.4
MISO: J2.4, J3.11, J6.11
MOSI: J2.6, J3.12, J6.12
SCLK: J2.2, J3.10, J6.10
V1P8ANA: J3.7, J5.2, J6.7
V1P8DIG: J3.9, J5.3, J6.9
VDD: J2.10, J2.12, J3.1, J4.1, J6.1
VDDIO: J4.3, J5.1
VDDIO_SEL: J3.3, J4.2, J6.3

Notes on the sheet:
Test Points

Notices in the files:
parts and their libraries:
SparkFun-Jumpers: Licensing: Creative Commons ShareAlike 4.0 International - https://creativecommons.org/licenses/by-sa/4.0
con-samtec-tmm: Copyright (C) 2013, Bob Starr
